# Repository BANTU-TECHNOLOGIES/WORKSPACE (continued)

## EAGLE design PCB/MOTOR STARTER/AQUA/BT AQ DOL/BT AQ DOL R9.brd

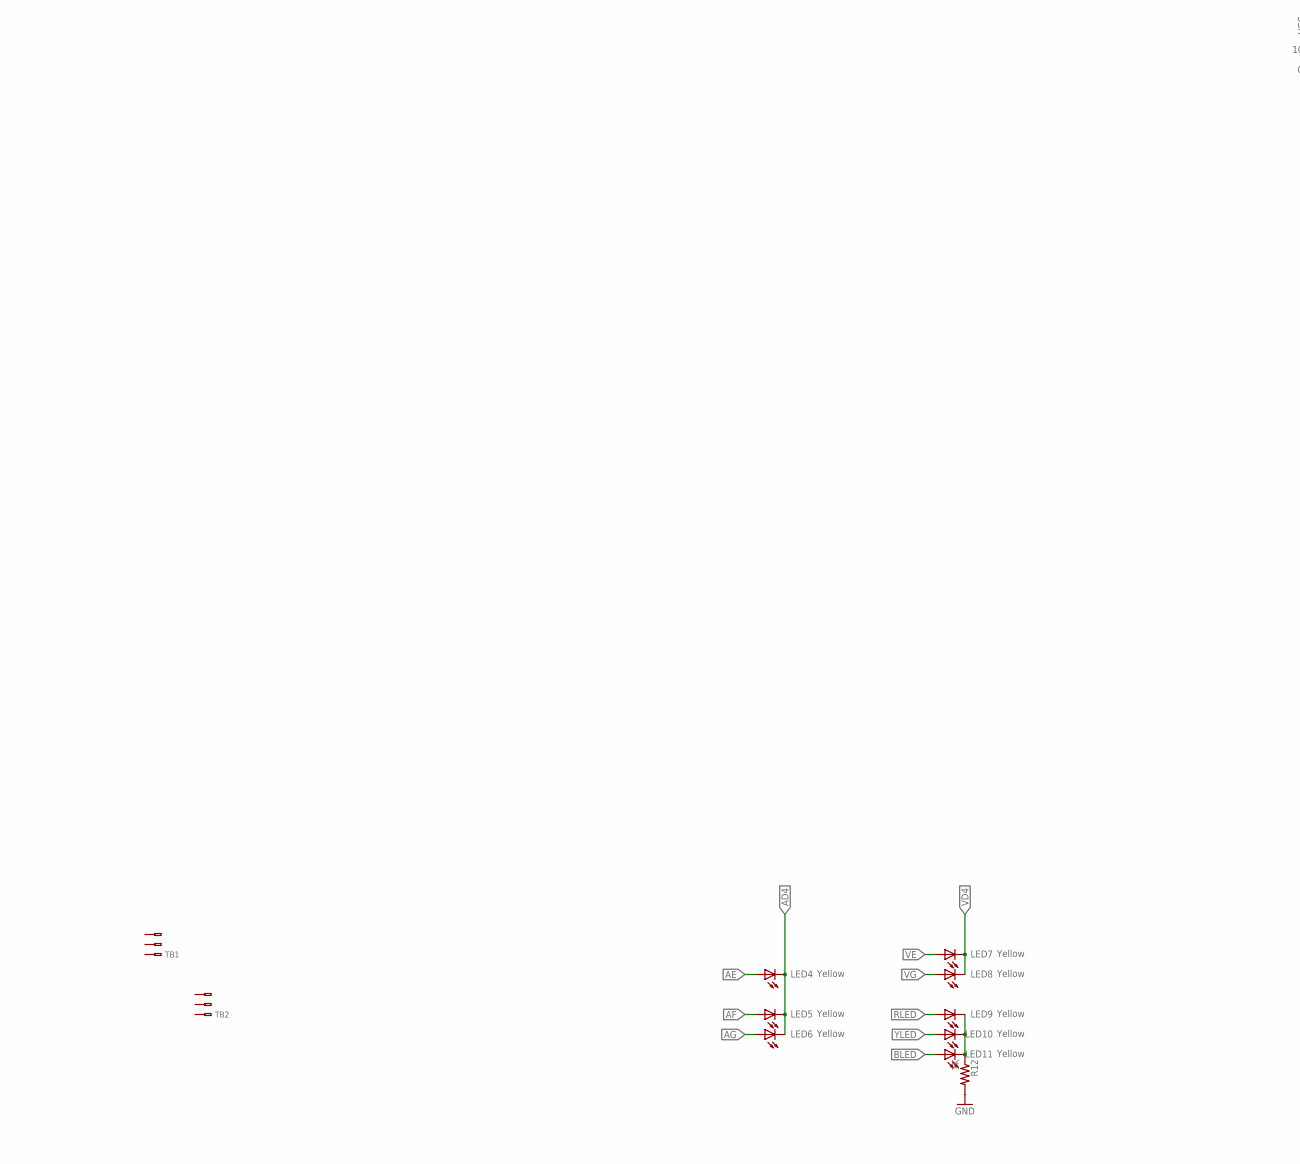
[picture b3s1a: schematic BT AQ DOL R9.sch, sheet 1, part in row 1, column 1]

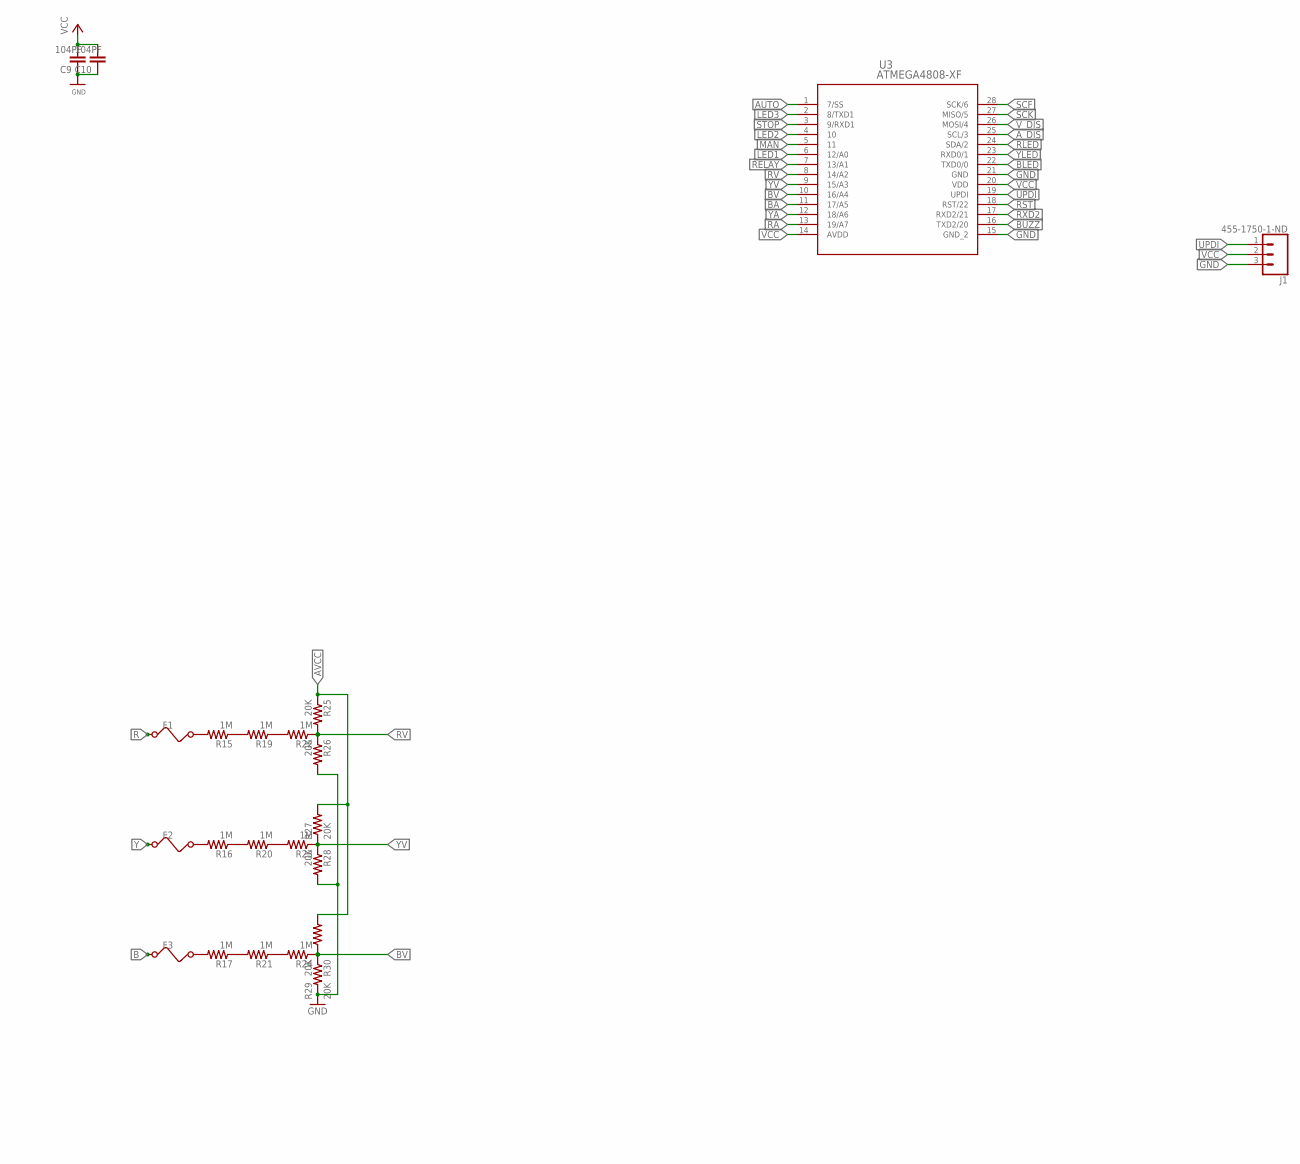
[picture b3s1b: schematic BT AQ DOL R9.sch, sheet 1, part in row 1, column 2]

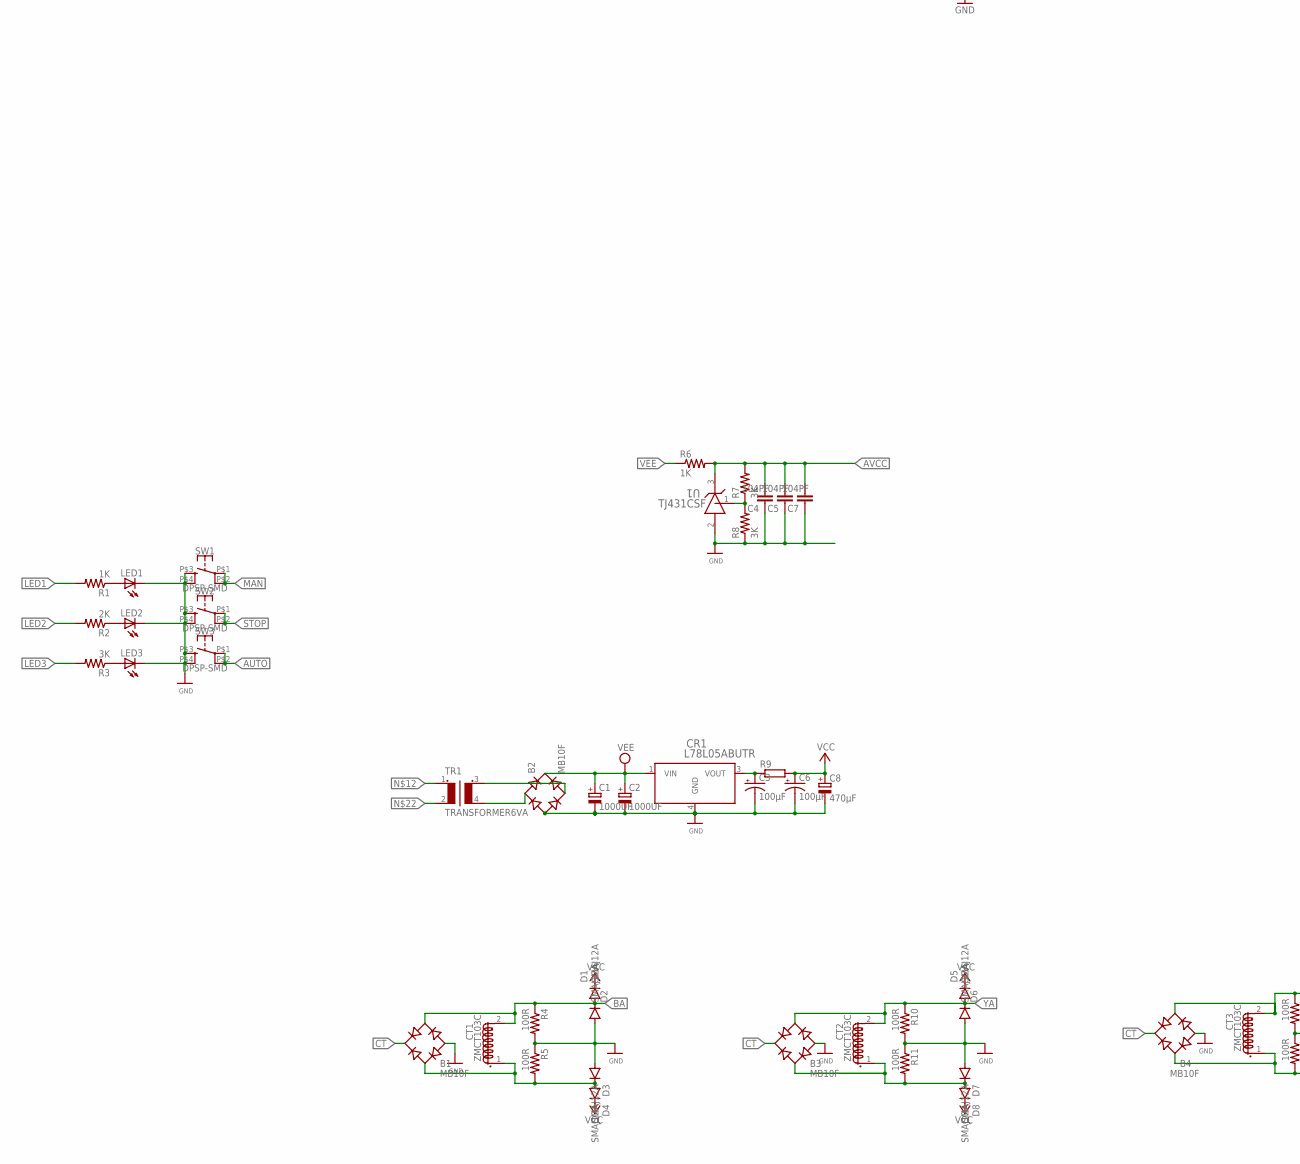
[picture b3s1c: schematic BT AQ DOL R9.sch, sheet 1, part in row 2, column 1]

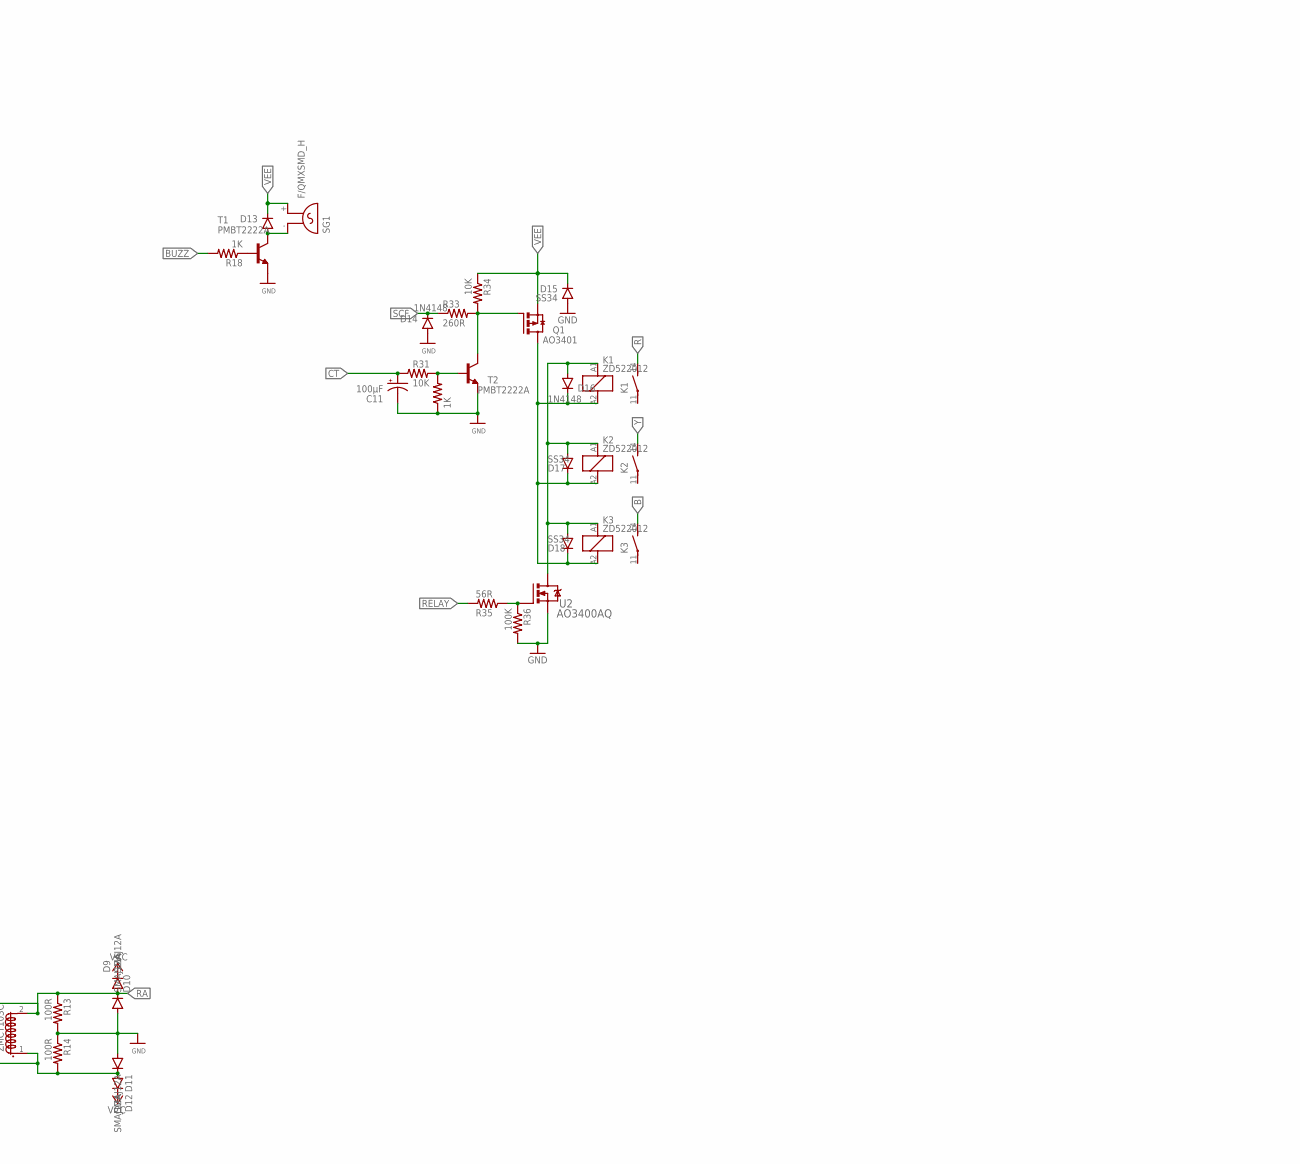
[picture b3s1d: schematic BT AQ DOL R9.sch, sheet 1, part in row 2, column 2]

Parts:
B1, B2, B3, B4: MB10F; SOIC-4
C1, C2: 1000UF; SANYO-OSCON_G
C3, C6, C11: 100μF; E2,5-6
C4, C5, C7, C9, C10: 104PF; C1206
C8: 470μF; E3,5-8
CR1: L78L05ABUTR; D2PAK
CT1, CT2, CT3: ZMCT103C
D1, D2, D3, D4, D5, D6, D7, D8, D9, D10, D11, D12: SMAJ12A; DO214AC
D13, D14, D16: 1N4148; MINIMELF
D15, D17, D18: SS34; DO214AC
F1, F2, F3: FUSESMD; WIRE
J1: 455-1750-1-ND; 1X03
K1, K2, K3: ZD522012; ZD2F
LED1, LED2, LED3: Blue; LED3MM
LED4, LED5, LED6, LED7, LED8, LED9, LED10, LED11: Yellow; LED3MM
Q1: AO3401; SUPER-SOT3
R1, R6, R12, R18, R32: 1K; M1206
R2: 2K; M1206
R3, R7, R8: 3K; M1206
R4, R5, R10, R11, R13, R14: 100R; M1206
R9: R-EU_R0603; R0603
R15, R16, R17, R19, R20, R21, R22, R23, R24: 1M; M1206
R25, R26, R27, R28, R29, R30: 20K; M1206
R31, R34: 10K; M1206
R33: 260R; M1206
R35: 56R; M1206
R36: 100K; M1206
SG1: F/QMXSMD_H; F/QMX_H
SW1, SW2, SW3: DPSP-SMD; B3F-40XX-ROUND-SMD
T1, T2: PMBT2222A; SC59-BEC
TB1, TB2: TERMINAL_BLOCK_3950/3; 950/3
TR1: TRANSFORMER6VA; 440V12V6VA
U1: TJ431CSF; SOT-23
U2: AO3400AQ; SOT-23-3L_AOS
U3: ATMEGA4808-XF; SSOP28_SS_MCH

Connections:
AD4: LED4.K (C), LED5.K (C), LED6.K (C); also elsewhere on the board
AE: LED4.A; also elsewhere on the board
AF: LED5.A; also elsewhere on the board
AG: LED6.A; also elsewhere on the board
AUTO: SW3.P$1 (1), SW3.P$2 (2), U3.1 (7/SS)
AVCC: C4.2, C5.2, C7.2, R6.2, R7.2, R25.1, R27.2, R29.2, U1.3 (CATHODE)
A_DIS: U3.25 (SCL/3); also elsewhere on the board
B: F3.1, K3.14 (S)
BA: B1.~2 (AC2), CT1.2 (S1.2), D1.A, D2.C, R4.1, U3.11 (17/A5)
BLED: LED11.A, U3.22 (TXD0/0)
BUZZ: R18.2, U3.16 (TXD2/20)
BV: R24.1, R29.1, R30.1, U3.10 (16/A4)
CT: B1.+, B3.+, B4.+, C11.+, R31.1
GND: B1.-, B2.-, B3.-, B4.-, C1.-, C2.-, C3.-, C4.1, C5.1, C6.-, C7.1, C8.-, C9.1, C10.1, C11.-, CR1.4 (GND), D2.A, D3.A, D6.A, D7.A, D10.A, D11.A, D14.A, D15.A, J1.3, LED1.K (C), LED2.K (C), LED3.K (C), R4.2, R5.1, R8.1, R10.2, R11.1, R12.2, R13.2, R14.1, R26.2, R28.2, R30.2, R32.1, R36.2, SW1.P$3 (3), SW1.P$4 (4), SW2.P$3 (3), SW2.P$4 (4), SW3.P$3 (3), SW3.P$4 (4), T1.E, T2.E, U1.2 (ANODE), U2.S, U3.15 (GND_2), U3.21 (GND); also elsewhere on the board
LED1: R1.2, U3.6 (12/A0)
LED2: R2.2, U3.4 (10)
LED3: R3.2, U3.2 (8/TXD1)
MAN: SW1.P$1 (1), SW1.P$2 (2), U3.5 (11)
unnamed: R19.1, R22.2
unnamed: B2.~1 (AC1), TR1.4 (S2)
unnamed: D13.A, SG1.- (1), T1.C
unnamed: R18.1, T1.B
unnamed: R21.1, R24.2
unnamed: R35.1, R36.1, U2.G
unnamed: C3.+, CR1.3 (VOUT), R9.1
unnamed: LED3.A, R3.1
unnamed: B2.~2 (AC2), TR1.3 (S1)
unnamed: R15.1, R19.2
unnamed: F1.2, R15.2, TR1.1
unnamed: LED2.A, R2.1
unnamed: R16.1, R20.2
unnamed: R17.1, R21.2
unnamed: D16.A, D17.A, D18.A, K1.A1 (1), K2.A1 (1), K3.A1 (1), U2.D
unnamed: Q1.1 (G), R33.2, R34.2, T2.C
unnamed: R20.1, R23.2
unnamed: D16.C, D17.C, D18.C, K1.A2 (2), K2.A2 (2), K3.A2 (2), Q1.3 (D)
unnamed: R7.1, R8.2, U1.1 (REF)
unnamed: F2.2, R16.2, TR1.2
unnamed: B1.~1 (AC1), CT1.1 (S1.1), D3.C, D4.A, R5.2
unnamed: F3.2, R17.2
unnamed: R31.2, R32.2, T2.B
unnamed: LED9.K (C), LED10.K (C), LED11.K (C), R12.1
unnamed: LED1.A, R1.1
unnamed: B3.~1 (AC1), CT2.1 (S1.1), D7.C, D8.A, R11.2
unnamed: B4.~1 (AC1), CT3.1 (S1.1), D11.C, D12.A, R14.2
R: F1.1, K1.14 (S)
RA: B4.~2 (AC2), CT3.2 (S1.2), D9.A, D10.C, R13.1, U3.13 (19/A7)
RELAY: R35.2, U3.7 (13/A1)
RLED: LED9.A, U3.24 (SDA/2)
RST: U3.18 (RST/22)
RV: R22.1, R25.2, R26.1, U3.8 (14/A2)
RXD2: U3.17 (RXD2/21)
SCF: D14.C, R33.1, U3.28 (SCK/6)
SCK: U3.27 (MISO/5); also elsewhere on the board
STOP: SW2.P$1 (1), SW2.P$2 (2), U3.3 (9/RXD1)
UPDI: J1.1, U3.19 (UPDI)
VCC: C6.+, C8.+, C9.2, C10.2, D1.C, D4.C, D5.C, D8.C, D9.C, D12.C, J1.2, R9.2, U3.14 (AVDD), U3.20 (VDD); also elsewhere on the board
VD4: LED7.K (C), LED8.K (C); also elsewhere on the board
VE: LED7.A; also elsewhere on the board
VEE: B2.+, C1.+, C2.+, CR1.1 (VIN), D13.C, D15.C, Q1.2 (S), R6.1, R34.1, SG1.+ (2)
VG: LED8.A; also elsewhere on the board
V_DIS: U3.26 (MOSI/4); also elsewhere on the board
Y: F2.1, K2.14 (S)
YA: B3.~2 (AC2), CT2.2 (S1.2), D5.A, D6.C, R10.1, U3.12 (18/A6)
YLED: LED10.A, U3.23 (RXD0/1)
YV: R23.1, R27.1, R28.1, U3.9 (15/A3)

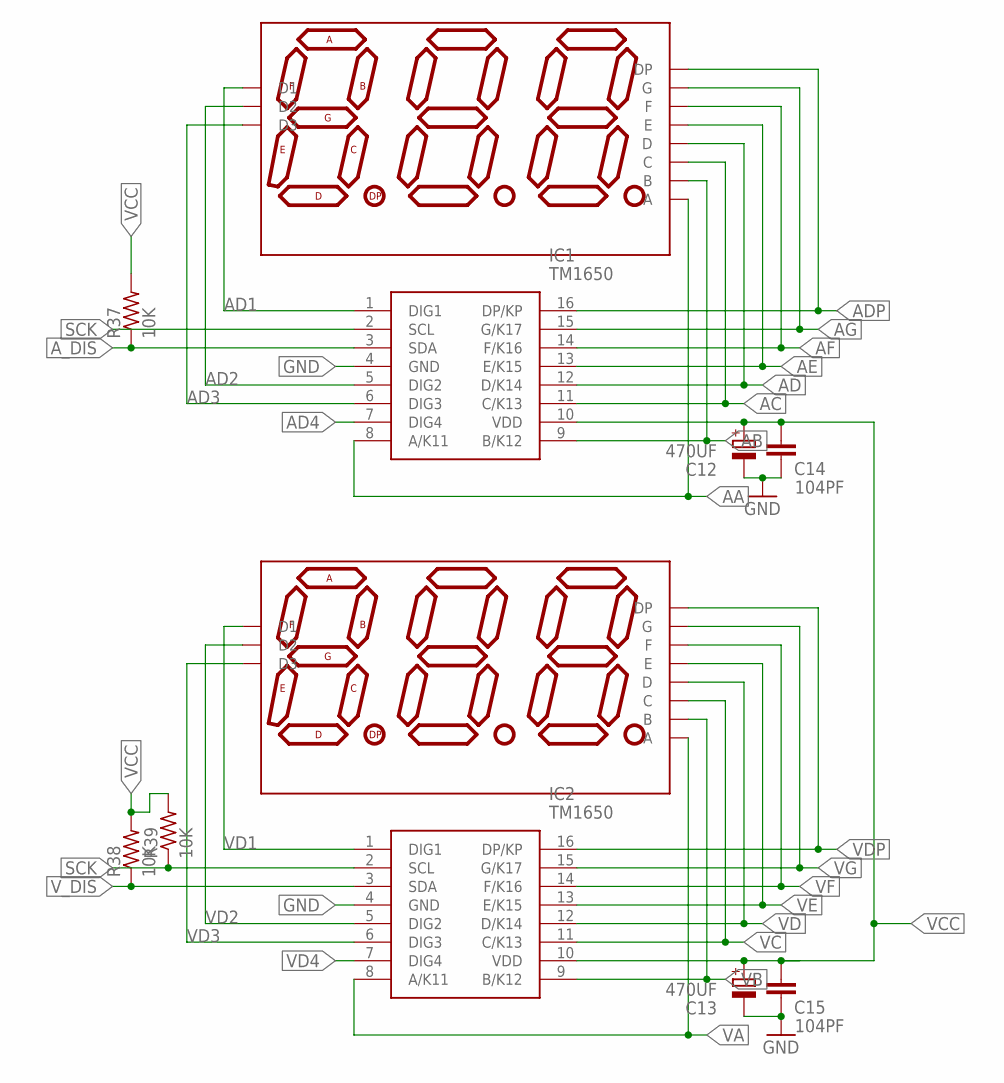
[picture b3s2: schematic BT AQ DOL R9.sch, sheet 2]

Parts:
C12, C13: 470UF; E3,5-8
C14, C15: 104PF; C1206
D19, D20: SUNR036CC3D; 7S3D036_DIP
IC1, IC2: TM1650; SOIC127P604X185-16N
R37, R38, R39: 10K; M1206

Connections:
AA: D19.11 (A), IC1.8 (A/K11)
AB: D19.7 (B), IC1.9 (B/K12)
AC: D19.4 (C), IC1.11 (C/K13)
AD: D19.2 (D), IC1.12 (D/K14)
AD1: D19.12 (D1), IC1.1 (DIG1)
AD2: D19.9 (D2), IC1.5 (DIG2)
AD3: D19.8 (D3), IC1.6 (DIG3)
AD4: IC1.7 (DIG4); also elsewhere on the board
ADP: D19.3 (DP), IC1.16 (DP/KP)
AE: D19.1 (E), IC1.13 (E/K15); also elsewhere on the board
AF: D19.10 (F), IC1.14 (F/K16); also elsewhere on the board
AG: D19.5 (G), IC1.15 (G/K17); also elsewhere on the board
A_DIS: IC1.3 (SDA), R37.1; also elsewhere on the board
GND: C12.-, C13.-, C14.1, C15.1, IC1.4 (GND), IC2.4 (GND); also elsewhere on the board
SCK: IC1.2 (SCL), IC2.2 (SCL), R39.1; also elsewhere on the board
VA: D20.11 (A), IC2.8 (A/K11)
VB: D20.7 (B), IC2.9 (B/K12)
VC: D20.4 (C), IC2.11 (C/K13)
VCC: C12.+, C13.+, C14.2, C15.2, IC1.10 (VDD), IC2.10 (VDD), R37.2, R38.2, R39.2; also elsewhere on the board
VD: D20.2 (D), IC2.12 (D/K14)
VD1: D20.12 (D1), IC2.1 (DIG1)
VD2: D20.9 (D2), IC2.5 (DIG2)
VD3: D20.8 (D3), IC2.6 (DIG3)
VD4: IC2.7 (DIG4); also elsewhere on the board
VDP: D20.3 (DP), IC2.16 (DP/KP)
VE: D20.1 (E), IC2.13 (E/K15); also elsewhere on the board
VF: D20.10 (F), IC2.14 (F/K16)
VG: D20.5 (G), IC2.15 (G/K17); also elsewhere on the board
V_DIS: IC2.3 (SDA), R38.1; also elsewhere on the board

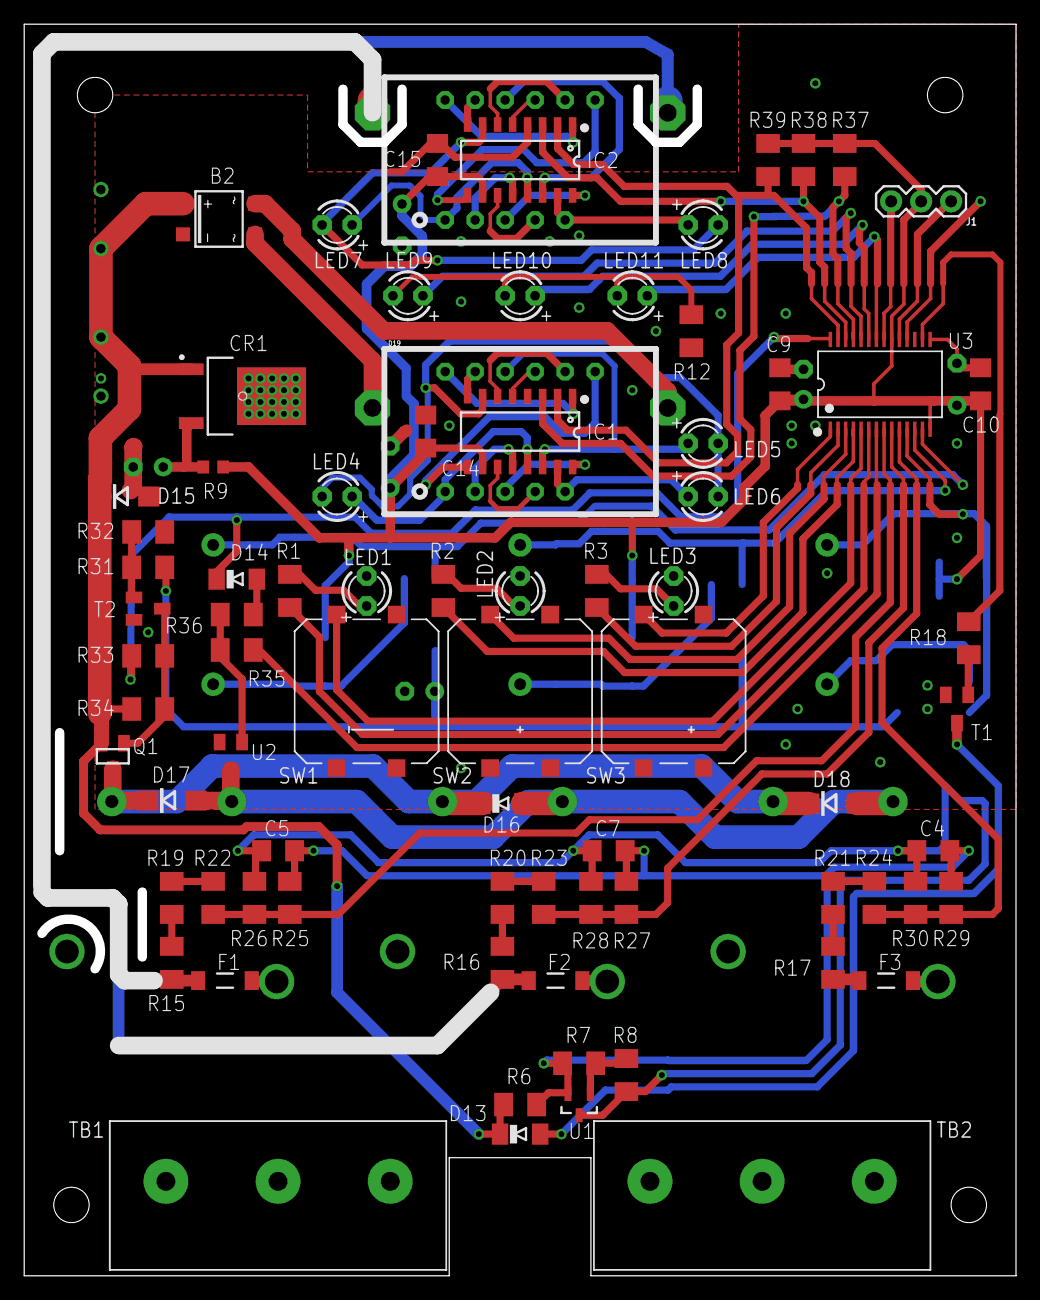
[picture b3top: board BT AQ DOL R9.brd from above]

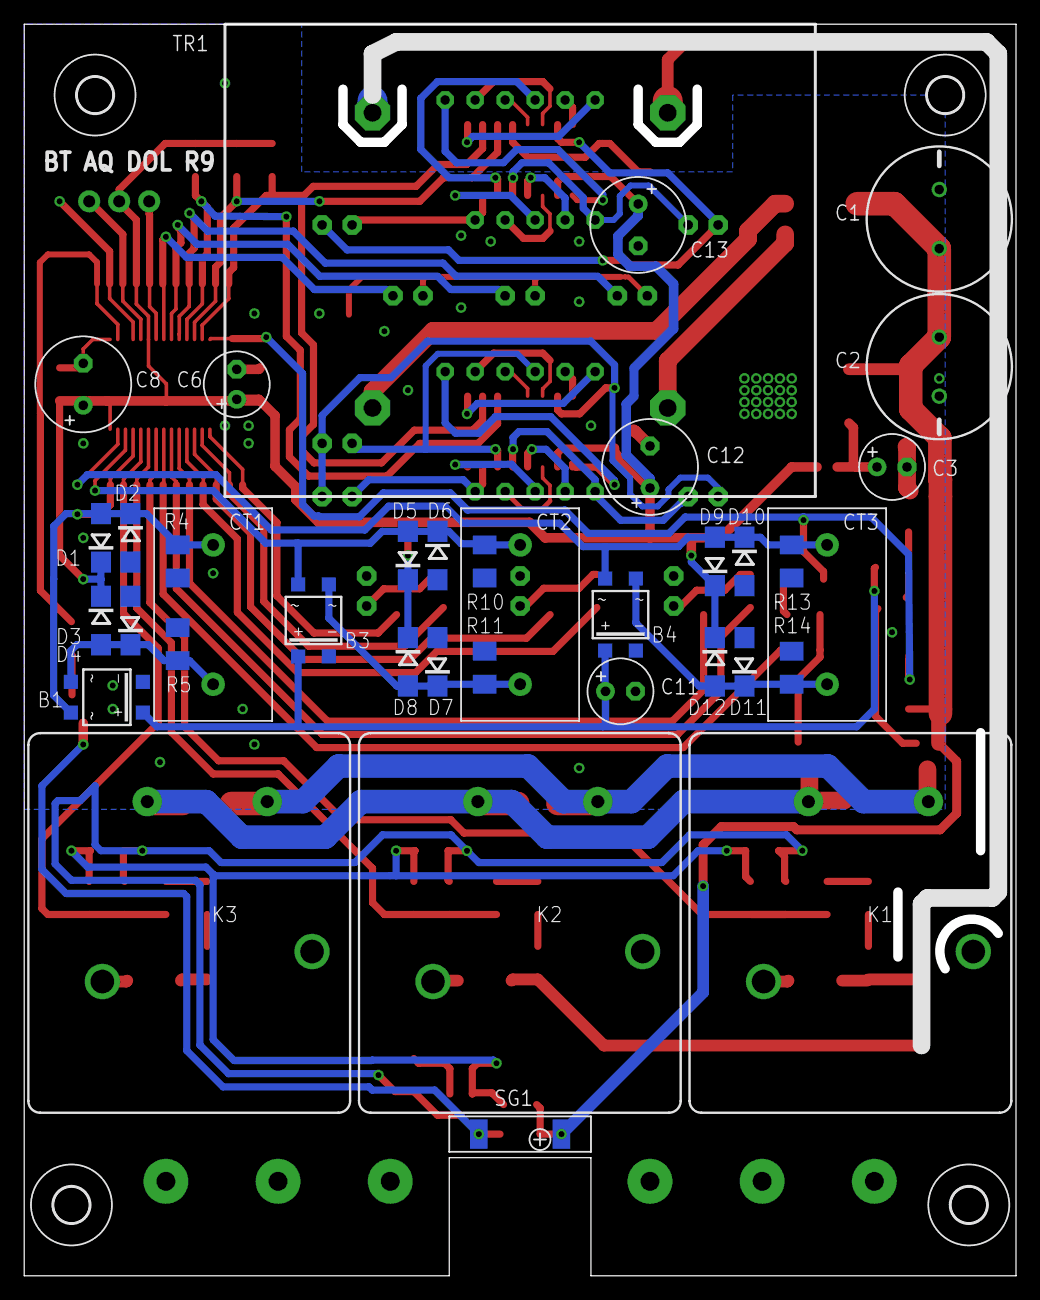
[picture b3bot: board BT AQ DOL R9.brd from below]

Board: 2 copper layers, 84.0 x 106.0 mm, 119 parts (41 on the bottom side), 81 nets.

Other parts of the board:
U$5, U$6, U$17, U$29: 3,0

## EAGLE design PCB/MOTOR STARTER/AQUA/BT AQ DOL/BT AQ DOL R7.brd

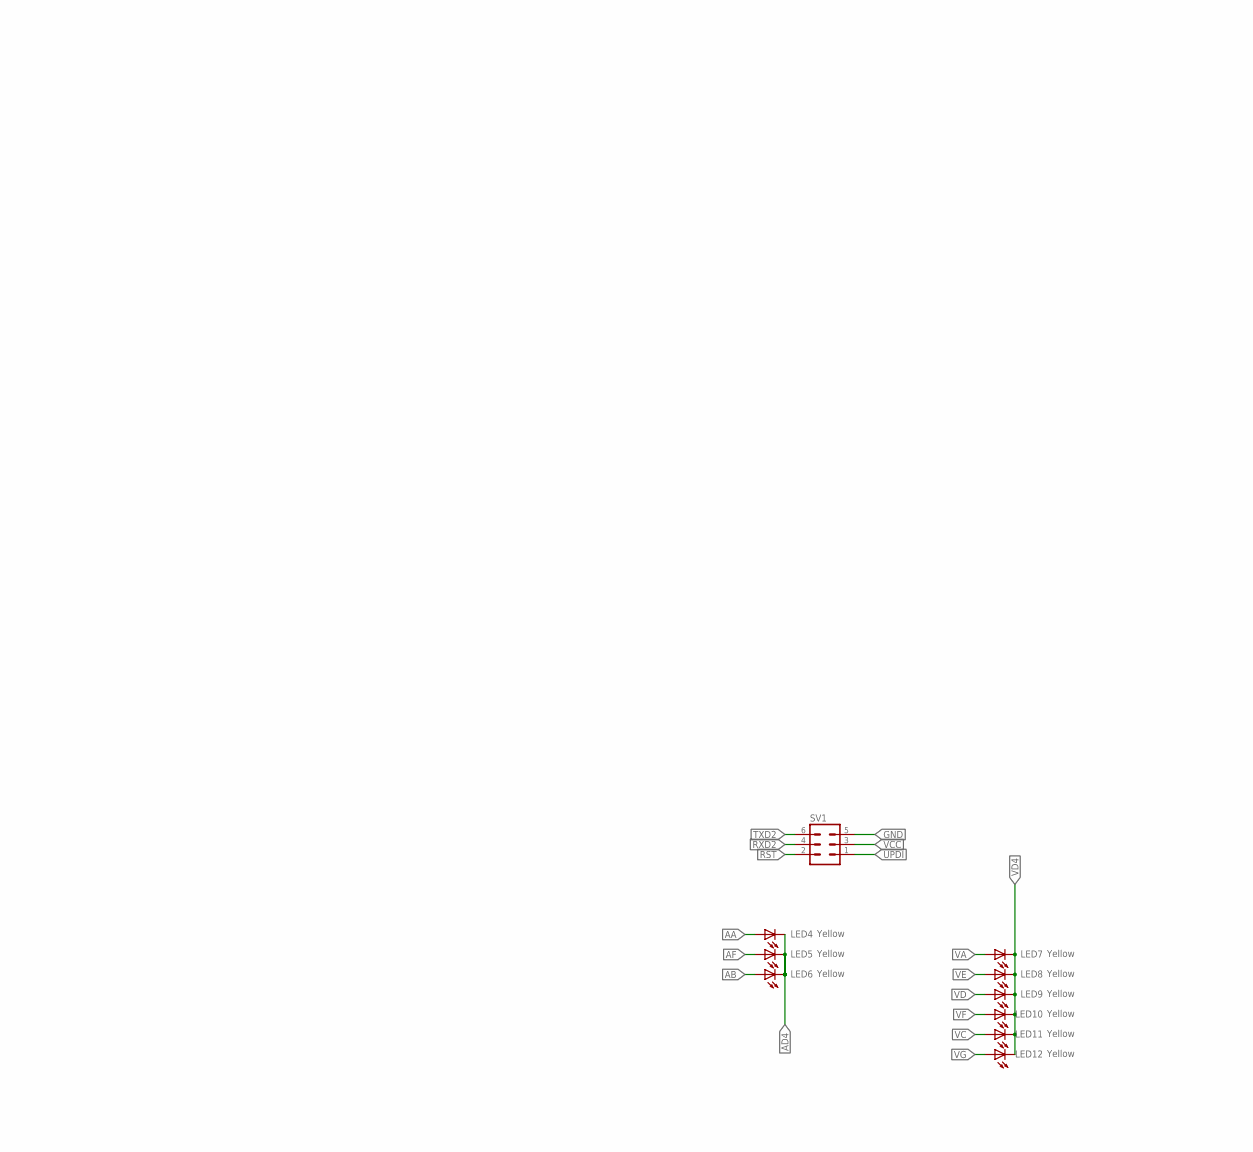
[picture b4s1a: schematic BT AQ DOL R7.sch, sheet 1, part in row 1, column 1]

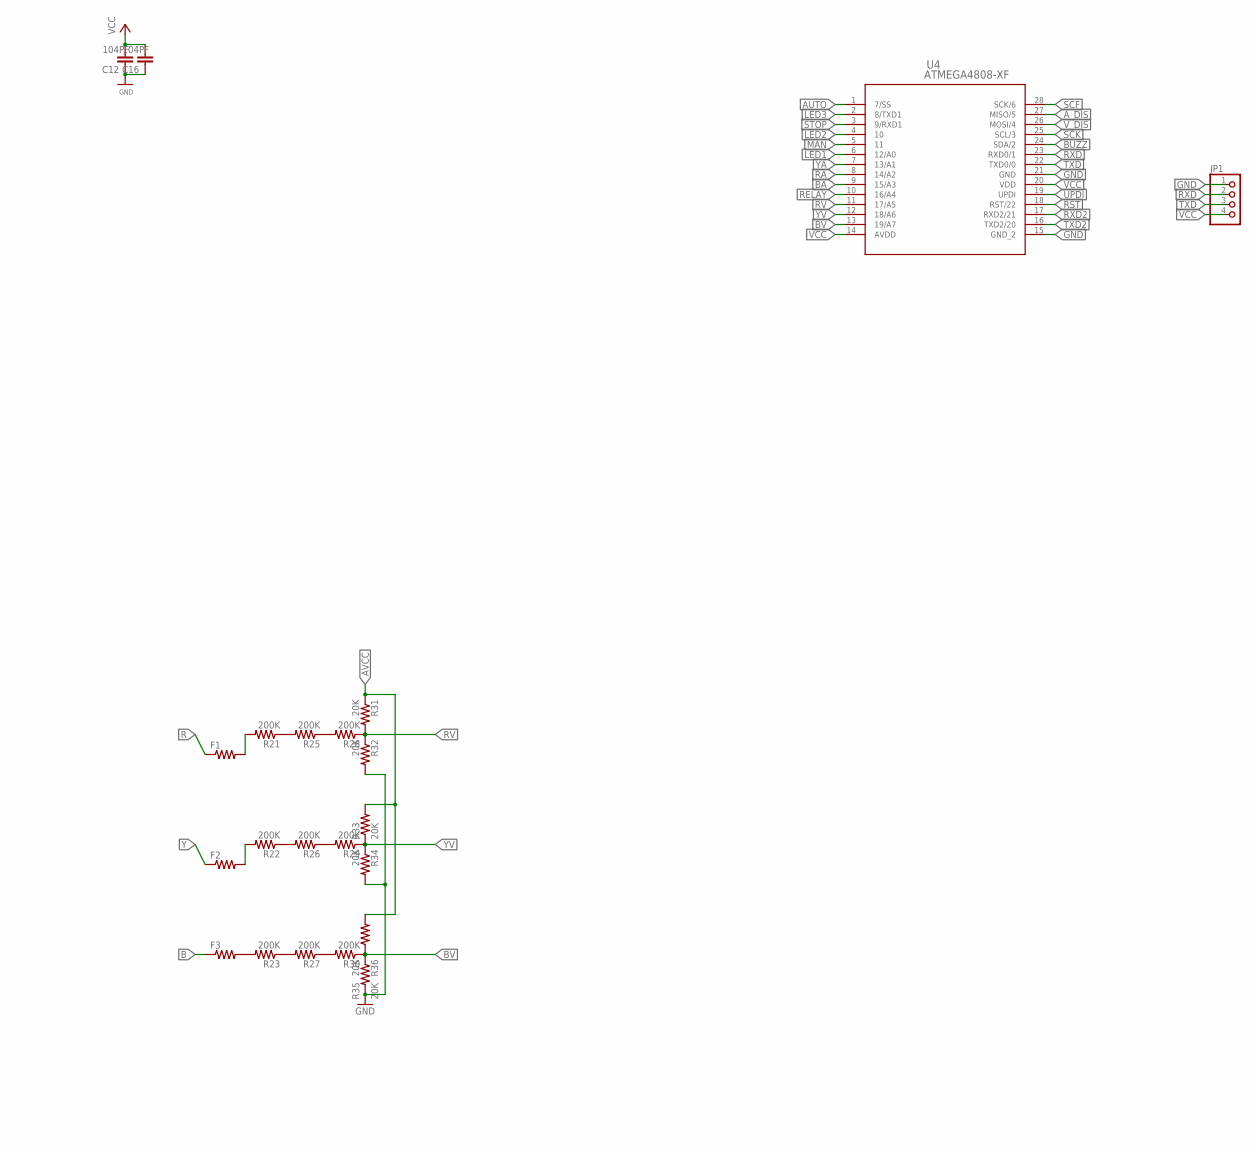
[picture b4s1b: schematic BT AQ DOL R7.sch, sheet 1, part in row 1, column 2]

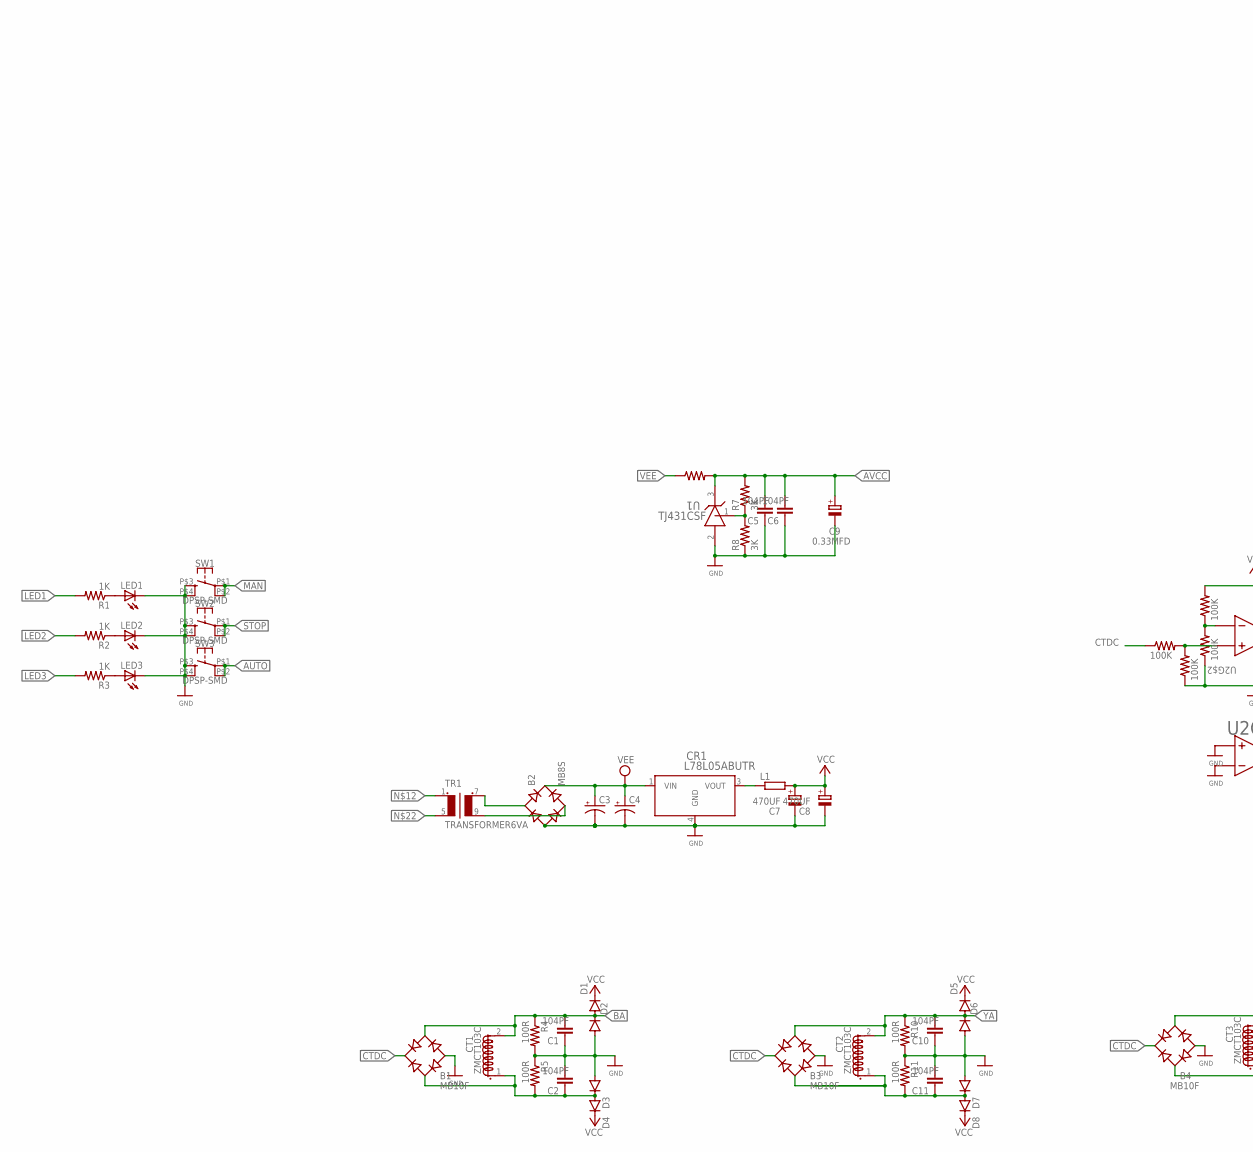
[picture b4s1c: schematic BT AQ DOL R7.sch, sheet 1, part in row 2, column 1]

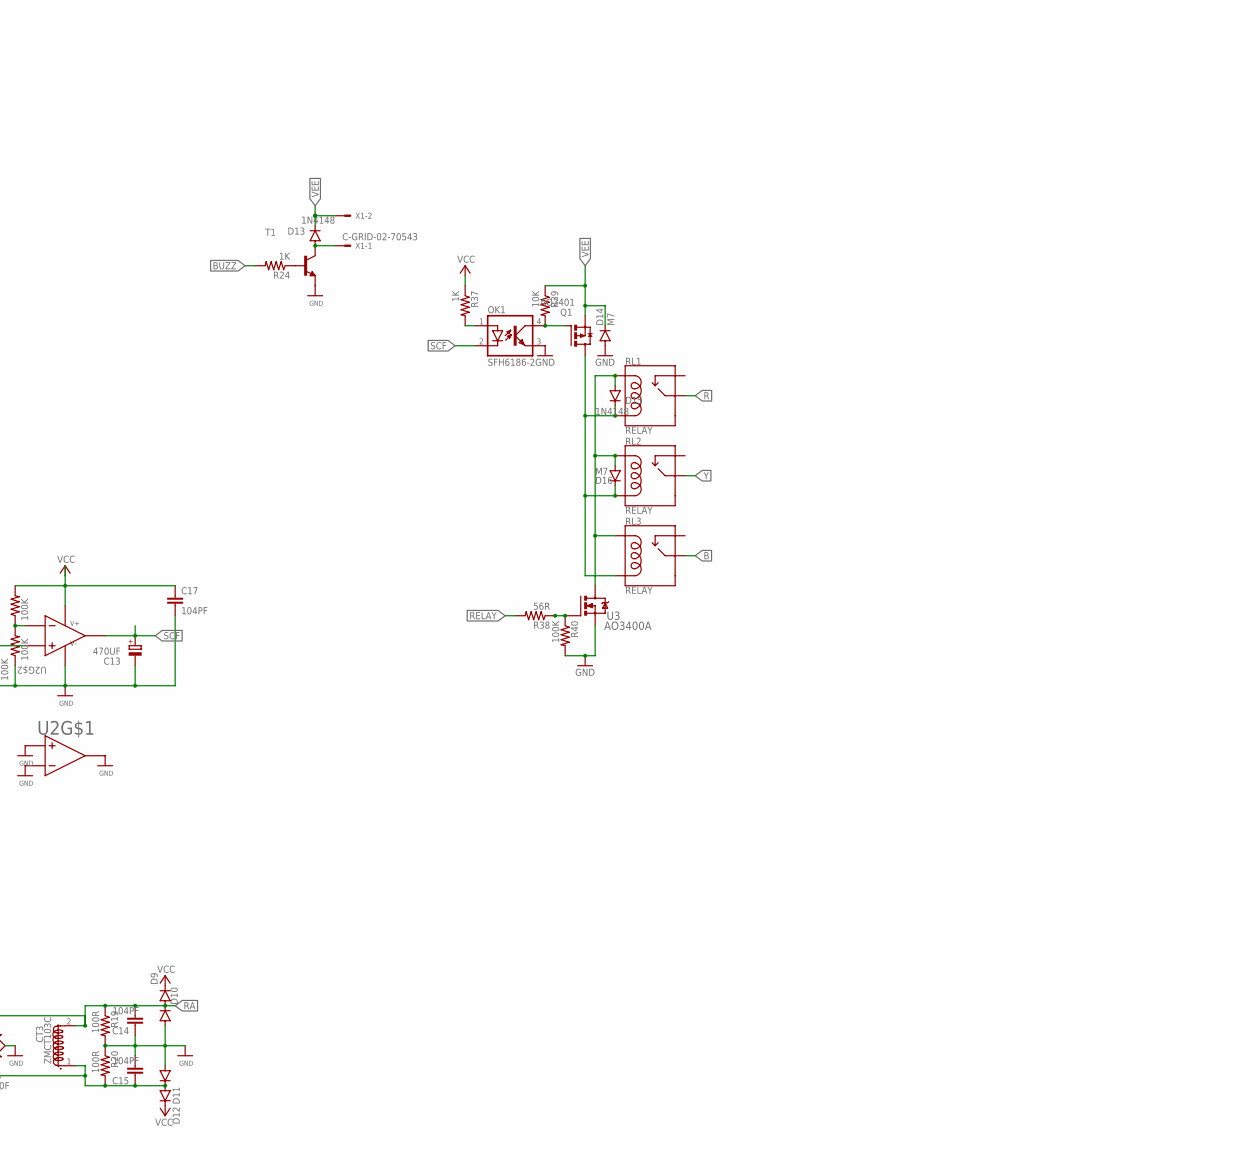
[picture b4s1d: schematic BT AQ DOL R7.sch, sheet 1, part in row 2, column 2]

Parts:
B1, B3, B4: MB10F; SOIC-4
B2: MB8S; SOIC-4
C1, C2, C5, C6, C10, C11, C12, C14, C15, C16, C17: 104PF; C1206
C3, C4: CPOL-USE3.5-10; E3,5-10
C7, C8, C13: 470UF; E3,5-8
C9: 0.33MFD; E2,5-5
CR1: L78L05ABUTR; D2PAK
CT1, CT2, CT3: ZMCT103C
D1, D2, D3, D4, D5, D6, D7, D8, D9, D10, D11, D12: DIODE-DO214AC; DO214AC
D13, D15: 1N4148; MINIMELF
D14: M7; DO-214AA
D16: M7; DO214AC
F1, F2, F3: R-US_MELF0204W; MINI_MELF-0204W
JP1: PINHD-1X4; 1X04
L1: R-EU_R0603; R0603
LED1, LED2, LED3: Blue; LED3MM
LED4, LED5, LED6, LED7, LED8, LED9, LED10, LED11, LED12: Yellow; LED3MM
OK1: SFH6186-2; SMD4-7
Q1: AO3401; SUPER-SOT3
R1, R2, R3, R24, R37: 1K; M1206
R4, R5, R10, R11, R19, R20: 100R; M1206
R6, R39: 10K; M1206
R7, R8: 3K; M1206
R12, R13, R14, R15, R40: 100K; M1206
R21, R22, R23, R25, R26, R27, R28, R29, R30: 200K; M1206
R31, R32, R33, R34, R35, R36: 20K; M1206
R38: 56R; M1206
RL1, RL2, RL3: RELAY; DT81_RECTANGULAR
SV1: MA03-2
SW1, SW2, SW3: DPSP-SMD; B3F-40XX-ROUND-SMD
T1: MMUN2213LT1-NPN-SC59-BEC; SC59-BEC
TR1: TRANSFORMER6VA; 440V12V6VA
U1: TJ431CSF; SOT-23
U2: LM393DG; SOIC8_ONS
U3: AO3400A; SOT-23-3L_AOS
U4: ATMEGA4808-XF; SSOP28_SS_MCH
X1: C-GRID-02-70543; 70543-02

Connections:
AA: LED4.A; also elsewhere on the board
AB: LED6.A; also elsewhere on the board
AD4: LED4.K (C), LED5.K (C), LED6.K (C); also elsewhere on the board
AF: LED5.A; also elsewhere on the board
AUTO: SW3.P$1 (1), SW3.P$2 (2), U4.1 (7/SS)
AVCC: C5.2, C6.2, C9.+, R6.2, R7.2, R31.1, R33.2, R35.2, U1.3 (CATHODE)
A_DIS: U4.27 (MISO/5); also elsewhere on the board
B: F3.1, RL3.C (MAIN), RL3.C. (MAIN)
BA: B1.~2 (AC2), C1.2, CT1.2 (S1.2), D1.A, D2.C, R4.1, U4.9 (15/A3)
BUZZ: R24.2, U4.24 (SDA/2)
BV: R30.1, R35.1, R36.1, U4.13 (19/A7)
CTDC: B1.+, B3.+, B4.+, R12.1
GND: B1.-, B2.-, B3.-, B4.-, C1.1, C2.2, C3.-, C4.-, C5.1, C6.1, C7.-, C8.-, C9.-, C10.1, C11.2, C12.1, C13.-, C14.1, C15.2, C16.1, C17.2, CR1.4 (GND), D2.A, D3.A, D6.A, D7.A, D10.A, D11.A, D14.A, JP1.1, LED1.K (C), LED2.K (C), LED3.K (C), OK1.3 (EMIT), R4.2, R5.1, R8.1, R10.2, R11.1, R13.1, R15.1, R19.2, R20.1, R32.2, R34.2, R36.2, R40.2, SV1.5, SW1.P$3 (3), SW1.P$4 (4), SW2.P$3 (3), SW2.P$4 (4), SW3.P$3 (3), SW3.P$4 (4), T1.E, U1.2 (ANODE), U2.1 (1OUT), U2.2 (1IN-), U2.3 (1IN+), U2.4 (GND), U3.S, U4.15 (GND_2), U4.21 (GND); also elsewhere on the board
LED1: R1.2, U4.6 (12/A0)
LED2: R2.2, U4.4 (10)
LED3: R3.2, U4.2 (8/TXD1)
MAN: SW1.P$1 (1), SW1.P$2 (2), U4.5 (11)
unnamed: R25.1, R28.2
unnamed: B2.~2 (AC2), TR1.9 (S2)
unnamed: D13.A, T1.C, X1.1
unnamed: R24.1, T1.B
unnamed: R27.1, R30.2
unnamed: R38.1, R40.1, U3.G
unnamed: CR1.3 (VOUT), L1.1
unnamed: LED3.A, R3.1
unnamed: B2.~1 (AC1), TR1.7 (S1)
unnamed: R21.1, R25.2
unnamed: F1.2, R21.2, TR1.1
unnamed: LED2.A, R2.1
unnamed: R22.1, R26.2
unnamed: R23.1, R27.2
unnamed: OK1.1 (A), R37.2
unnamed: D15.A, D16.A, RL1.1 (COIL1), RL1.1. (COIL1), RL2.1 (COIL1), RL2.1. (COIL1), RL3.1 (COIL1), RL3.1. (COIL1), U3.D
unnamed: OK1.4 (COL), Q1.1 (G), R39.2
unnamed: R26.1, R29.2
unnamed: D15.C, D16.C, Q1.3 (D), RL1.2 (COIL2), RL1.2. (COIL2), RL2.2 (COIL2), RL2.2. (COIL2), RL3.2 (COIL2), RL3.2. (COIL2)
unnamed: R7.1, R8.2, U1.1 (REF)
unnamed: F2.2, R22.2, TR1.5 (P2)
unnamed: B1.~1 (AC1), C2.1, CT1.1 (S1.1), D3.C, D4.A, R5.2
unnamed: F3.2, R23.2
unnamed: LED1.A, R1.1
unnamed: B3.~1 (AC1), C11.1, CT2.1 (S1.1), D7.C, D8.A, R11.2
unnamed: R12.2, R13.2, U2.5 (2IN+)
unnamed: B4.~1 (AC1), C15.1, CT3.1 (S1.1), D11.C, D12.A, R20.2
R: F1.1, RL1.C (MAIN), RL1.C. (MAIN)
RA: B4.~2 (AC2), C14.2, CT3.2 (S1.2), D9.A, D10.C, R19.1, U4.8 (14/A2)
RELAY: R38.2, U4.10 (16/A4)
RST: SV1.2, U4.18 (RST/22)
RV: R28.1, R31.2, R32.1, U4.11 (17/A5)
RXD: JP1.2, U4.23 (RXD0/1)
RXD2: SV1.4, U4.17 (RXD2/21)
SCF: C13.+, OK1.2 (C), U2.7 (2OUT), U4.28 (SCK/6)
SCF_VCC: R14.1, R15.2, U2.6 (2IN-)
SCK: U4.25 (SCL/3); also elsewhere on the board
STOP: SW2.P$1 (1), SW2.P$2 (2), U4.3 (9/RXD1)
TXD: JP1.3, U4.22 (TXD0/0)
TXD2: SV1.6, U4.16 (TXD2/20)
UPDI: SV1.1, U4.19 (UPDI)
VA: LED7.A; also elsewhere on the board
VC: LED11.A; also elsewhere on the board
VCC: C7.+, C8.+, C12.2, C16.2, C17.1, D1.C, D4.C, D5.C, D8.C, D9.C, D12.C, JP1.4, L1.2, R14.2, R37.1, SV1.3, U2.8 (VCC), U4.14 (AVDD), U4.20 (VDD); also elsewhere on the board
VD: LED9.A; also elsewhere on the board
VD4: LED7.K (C), LED8.K (C), LED9.K (C), LED10.K (C), LED11.K (C), LED12.K (C); also elsewhere on the board
VE: LED8.A; also elsewhere on the board
VEE: B2.+, C3.+, C4.+, CR1.1 (VIN), D13.C, D14.C, Q1.2 (S), R6.1, R39.1, X1.2
VF: LED10.A; also elsewhere on the board
VG: LED12.A; also elsewhere on the board
V_DIS: U4.26 (MOSI/4); also elsewhere on the board
Y: F2.1, RL2.C (MAIN), RL2.C. (MAIN)
YA: B3.~2 (AC2), C10.2, CT2.2 (S1.2), D5.A, D6.C, R10.1, U4.7 (13/A1)
YV: R29.1, R33.1, R34.1, U4.12 (18/A6)
